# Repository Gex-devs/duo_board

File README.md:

# duo_board

## Custom Split keyboard with PS4 joystic as a mousepad.
* Left Side Only So far
* Firmware:= QMK

### PCB Board View

### Keymap View schema

### Main View schema

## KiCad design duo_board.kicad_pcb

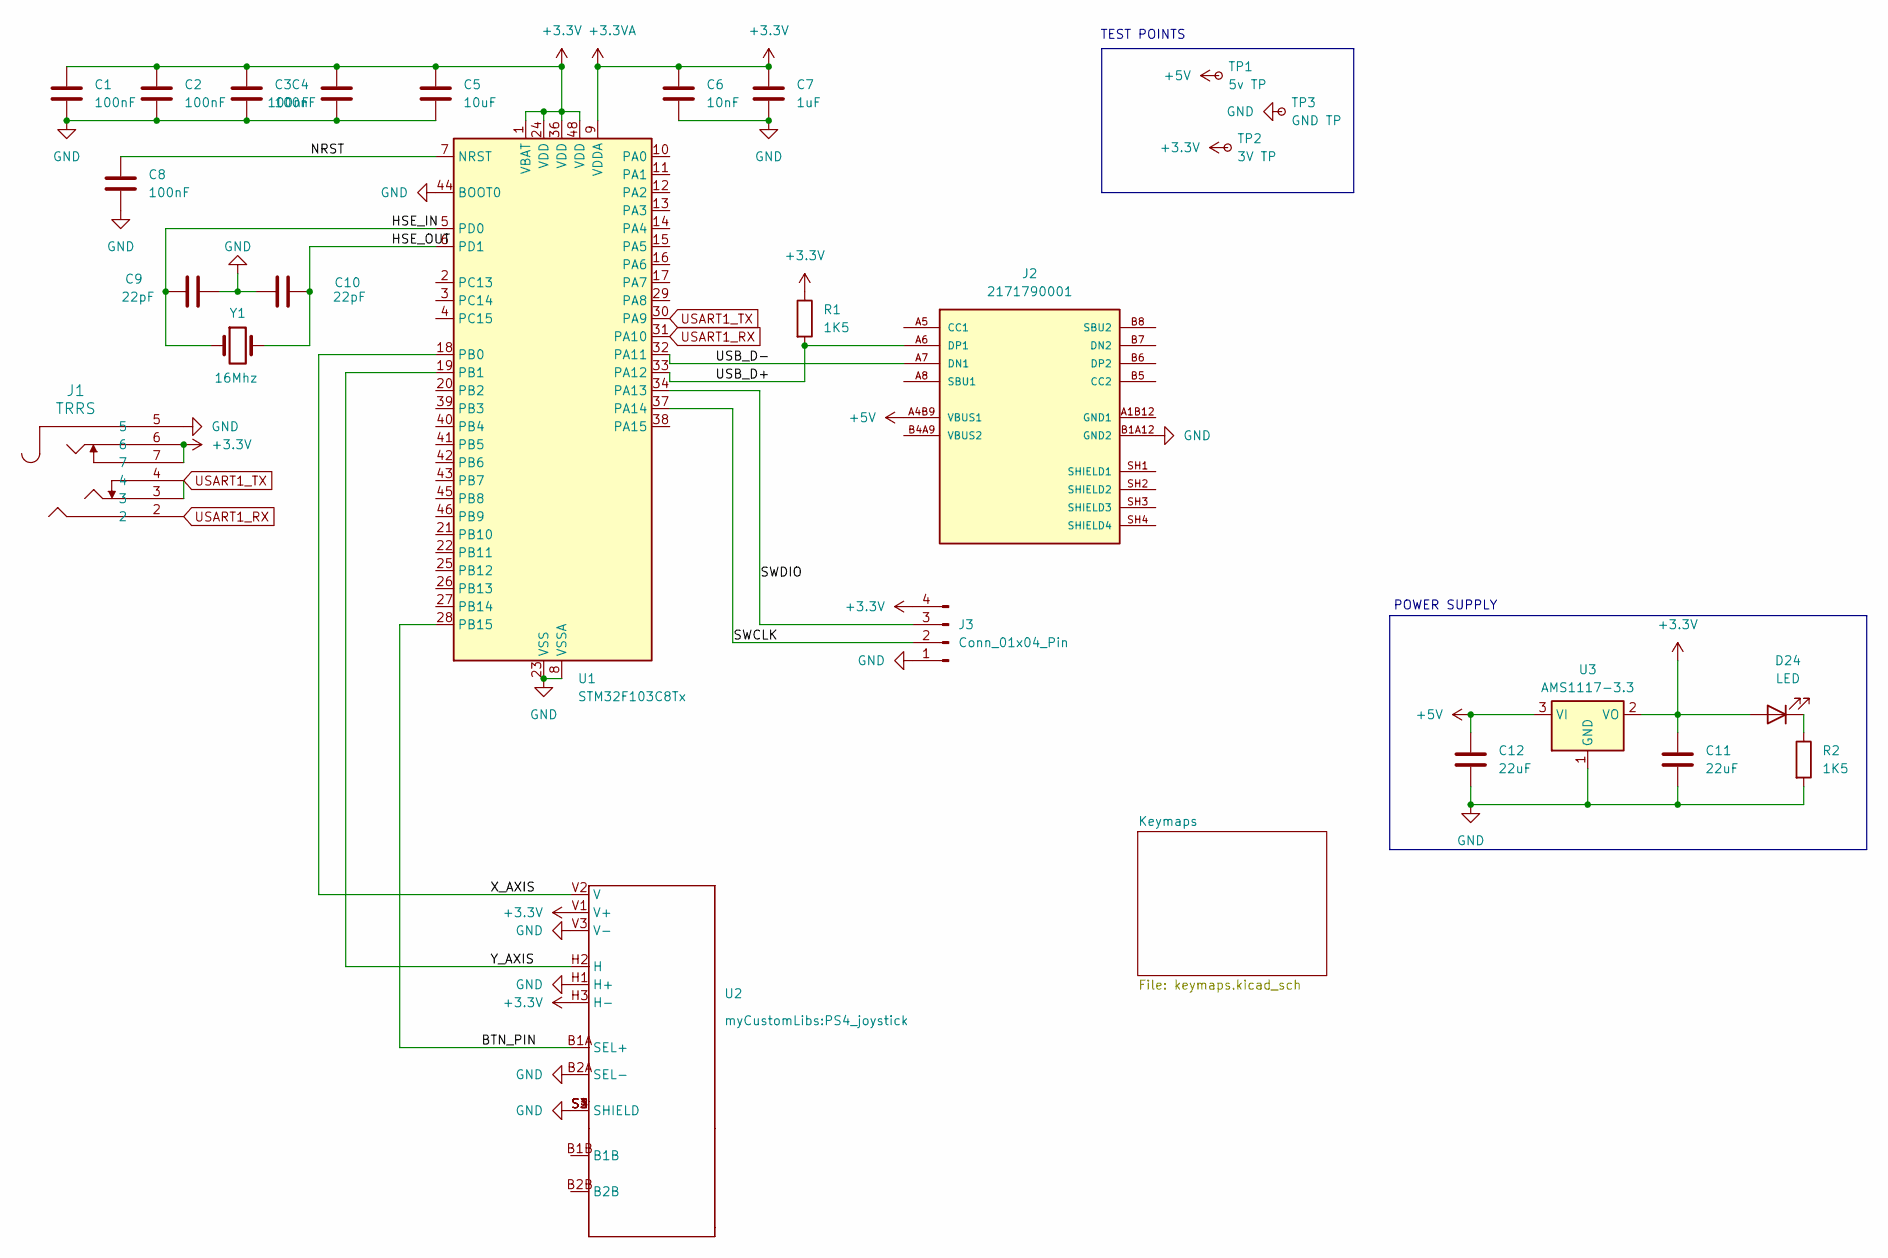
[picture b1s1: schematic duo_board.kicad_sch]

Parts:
C1, C2, C3, C4, C8: 100nF; C_Disc_D4.3mm_W1.9mm_P5.00mm
C5: 10uF; CP_Radial_Tantal_D5.5mm_P2.50mm
C6: 10nF; C_Disc_D4.3mm_W1.9mm_P5.00mm
C7: 1uF; C_Disc_D4.3mm_W1.9mm_P5.00mm
C9, C10: 22pF; C_Disc_D3.0mm_W1.6mm_P2.50mm
C11, C12: 22uF; C_Disc_D4.3mm_W1.9mm_P5.00mm
D24: LED; LED_0805_2012Metric
J1: TRRS; PJ-342B-TX-SMT_XKB
J2: 2171790001; MOLEX_2171790001; PARTREV A1
J3: Conn_01x04_Pin; JST_XH_B4B-XH-A_1x04_P2.50mm_Vertical
R1, R2: 1K5; R_Axial_DIN0207_L6.3mm_D2.5mm_P10.16mm_Horizontal
TP1: 5v TP; TestPoint_Pad_1.0x1.0mm
TP2: 3V TP; TestPoint_Pad_1.0x1.0mm
TP3: GND TP; TestPoint_Pad_1.0x1.0mm
U1: STM32F103C8Tx; LQFP-48_7x7mm_P0.5mm
U2: PS4_joystick
U3: AMS1117-3.3; SOT-223-3_TabPin2
Y1: 16Mhz; Crystal_HC49-4H_Vertical

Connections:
+3.3V: C1.1, C2.1, C3.1, C4.1, C5.1, C6.1, C7.1, C11.1, D24.2 (A), J1.6, J1.7, J3.4, R1.1, TP2.1, U1.1 (VBAT), U1.9 (VDDA), U1.24 (VDD), U1.36 (VDD), U1.48 (VDD), U2.H3 (H-), U2.V1 (V+), U3.2 (VO)
+5V: C12.2, J2.A4B9 (VBUS1), TP1.1, U3.3 (VI)
/BTN_PIN: U1.28 (PB15), U2.B1A (SEL+)
/HSE_IN: C9.2, U1.5 (PD0), Y1.1
/HSE_OUT: C10.1, U1.6 (PD1), Y1.2
/NRST: C8.1, U1.7 (NRST)
/SWCLK: J3.2, U1.37 (PA14)
/SWDIO: J3.3, U1.34 (PA13)
/USB_D+: J2.A6 (DP1), R1.2, U1.33 (PA12)
/USB_D-: J2.A7 (DN1), U1.32 (PA11)
/X_AXIS: U1.18 (PB0), U2.V2 (V)
/Y_AXIS: U1.19 (PB1), U2.H2 (H)
GND: C1.2, C2.2, C3.2, C4.2, C5.2, C6.2, C7.2, C8.2, C9.1, C10.2, C11.2, C12.1, J1.5, J2.B1A12 (GND2), J3.1, R2.2, TP3.1, U1.8 (VSSA), U1.23 (VSS), U1.35 (VSS), U1.44 (BOOT0), U1.47 (VSS), U2.B2A (SEL-), U2.H1 (H+), U2.S1 (SHIELD), U2.S2 (SHIELD), U2.S3 (SHIELD), U2.S4 (SHIELD), U2.V3 (V-), U3.1 (GND)
unnamed: D24.1 (K), R2.1
USART1_RX: J1.2, U1.31 (PA10)
USART1_TX: J1.3, J1.4, U1.30 (PA9)

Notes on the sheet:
TEST POINTS
POWER SUPPLY

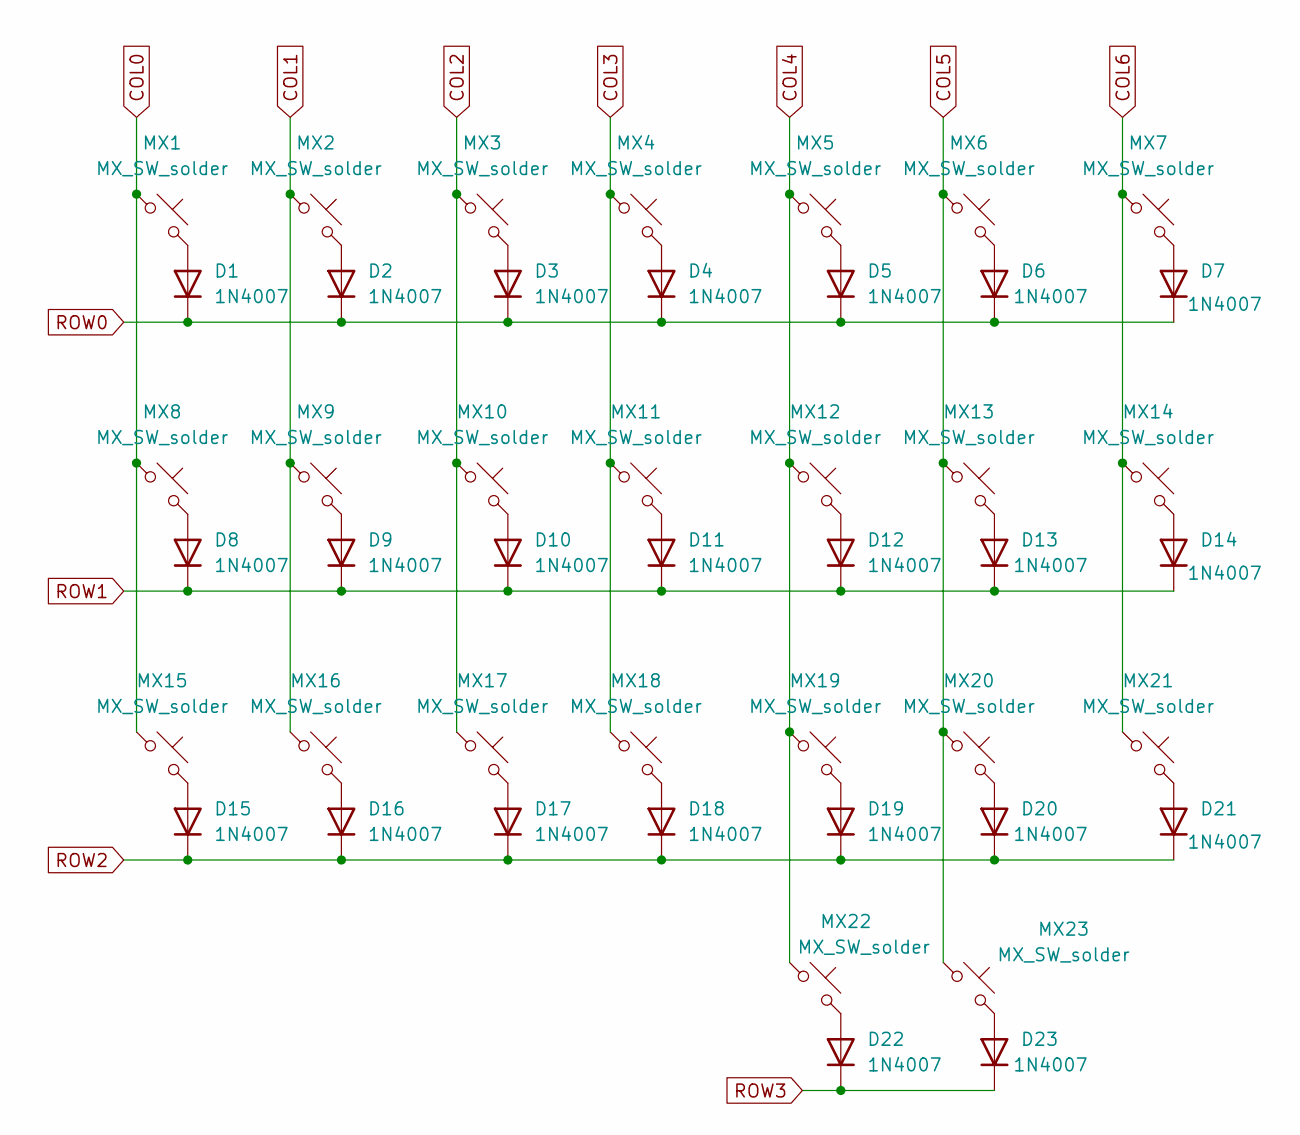
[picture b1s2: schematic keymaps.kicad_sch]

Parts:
D1, D2, D3, D4, D5, D6, D7, D8, D9, D10, D11, D12, D13, D14, D15, D16, D17, D18, D19, D20, D21, D22, D23: 1N4007; D_SMA
MX1, MX2, MX3, MX4, MX5, MX6, MX7, MX8, MX9, MX10, MX11, MX12, MX13, MX14, MX15, MX16, MX17, MX18, MX19, MX20, MX21, MX22: MX_SW_solder; SW_MX_1u
MX23: MX_SW_solder; SW_MX_1.75u

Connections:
COL0: MX1.1, MX8.1, MX15.1
COL1: MX2.1, MX9.1, MX16.1
COL2: MX3.1, MX10.1, MX17.1
COL3: MX4.1, MX11.1, MX18.1
COL4: MX5.1, MX12.1, MX19.1, MX22.1
COL5: MX6.1, MX13.1, MX20.1, MX23.1
COL6: MX7.1, MX14.1, MX21.1
unnamed: D1.2 (A), MX1.2
unnamed: D2.2 (A), MX2.2
unnamed: D3.2 (A), MX3.2
unnamed: D4.2 (A), MX4.2
unnamed: D5.2 (A), MX5.2
unnamed: D6.2 (A), MX6.2
unnamed: D7.2 (A), MX7.2
unnamed: D8.2 (A), MX8.2
unnamed: D9.2 (A), MX9.2
unnamed: D10.2 (A), MX10.2
unnamed: D11.2 (A), MX11.2
unnamed: D12.2 (A), MX12.2
unnamed: D13.2 (A), MX13.2
unnamed: D14.2 (A), MX14.2
unnamed: D15.2 (A), MX15.2
unnamed: D16.2 (A), MX16.2
unnamed: D17.2 (A), MX17.2
unnamed: D18.2 (A), MX18.2
unnamed: D19.2 (A), MX19.2
unnamed: D20.2 (A), MX20.2
unnamed: D21.2 (A), MX21.2
unnamed: D22.2 (A), MX22.2
unnamed: D23.2 (A), MX23.2
ROW0: D1.1 (K), D2.1 (K), D3.1 (K), D4.1 (K), D5.1 (K), D6.1 (K), D7.1 (K)
ROW1: D8.1 (K), D9.1 (K), D10.1 (K), D11.1 (K), D12.1 (K), D13.1 (K), D14.1 (K)
ROW2: D15.1 (K), D16.1 (K), D17.1 (K), D18.1 (K), D19.1 (K), D20.1 (K), D21.1 (K)
ROW3: D22.1 (K), D23.1 (K)

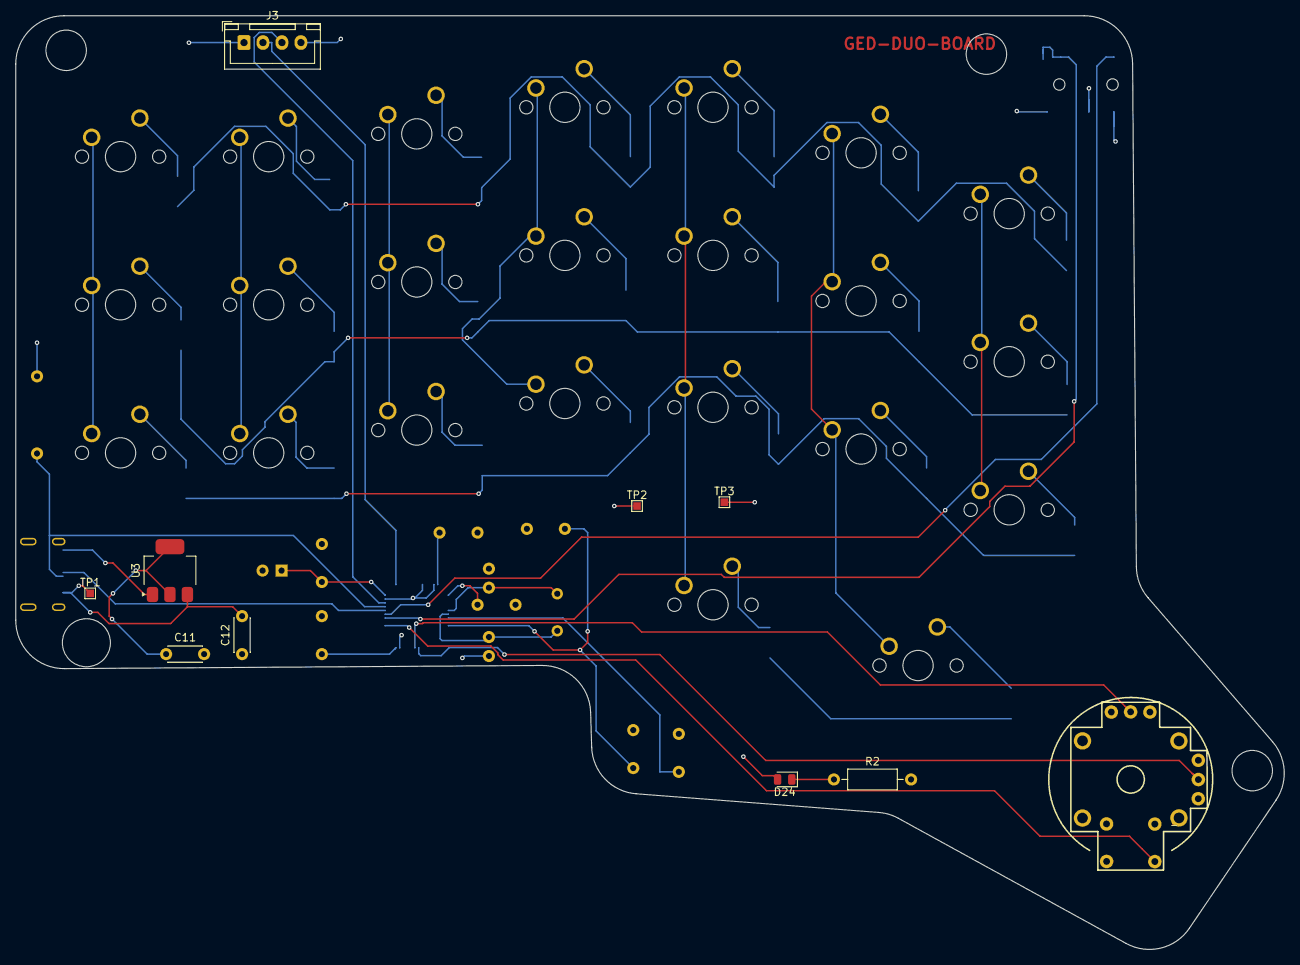
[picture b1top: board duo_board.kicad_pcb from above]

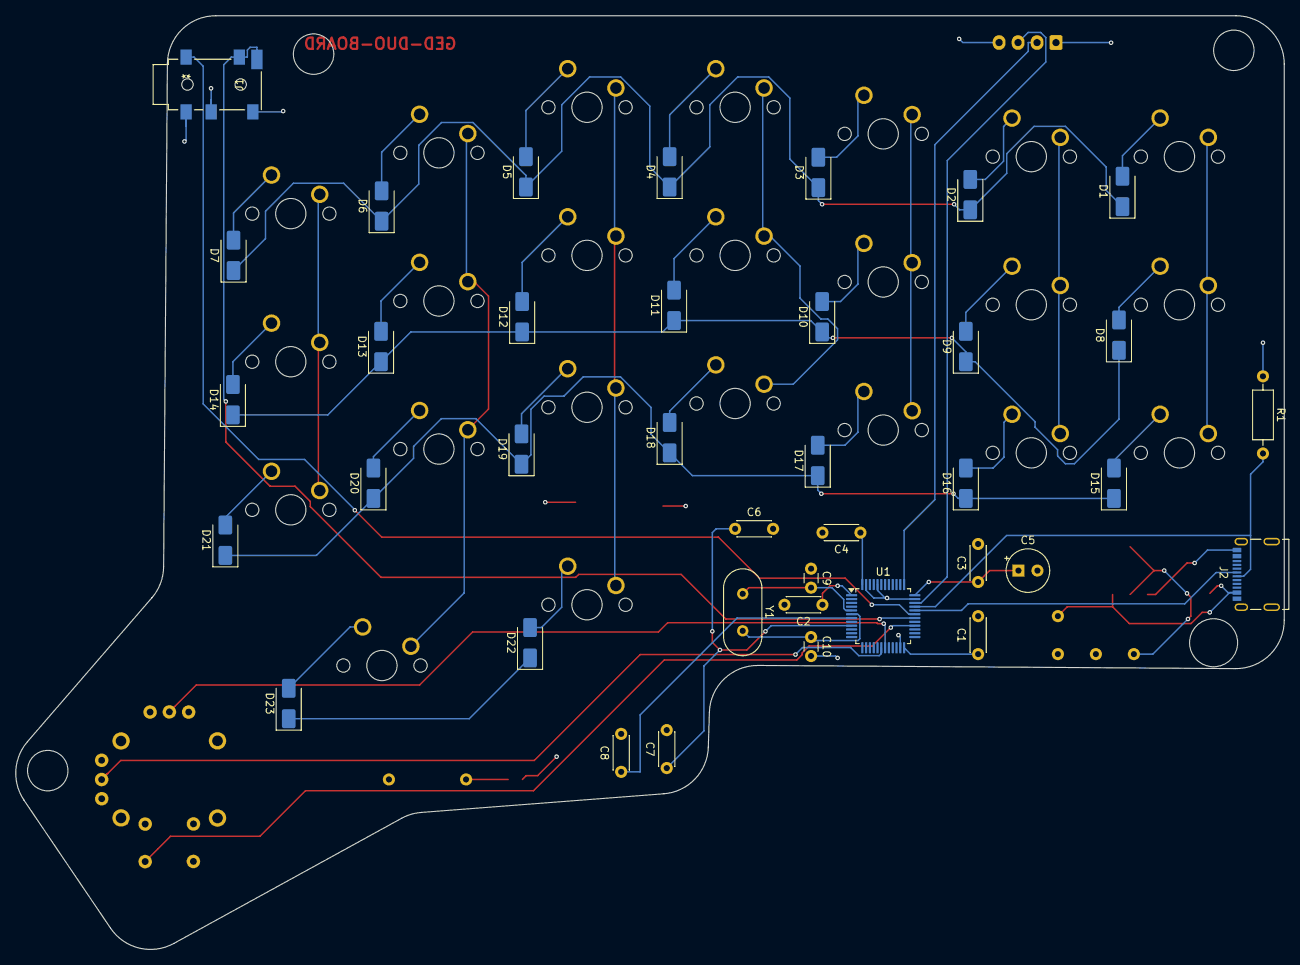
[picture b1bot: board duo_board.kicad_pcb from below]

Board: 4 copper layers, 167.0 x 122.9 mm, 71 parts (38 on the bottom side), 50 nets.

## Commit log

2024-10-10 duo board
2024-10-10 completed MCU power supply
2024-10-11 routed, ready for production?
2024-10-11 updated readme and added images
2024-10-14 added firmware submodule and updated pcb
